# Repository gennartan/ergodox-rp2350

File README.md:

# ErgoDox Custom Keyboard

## 1. Introduction

This project is a custom split ErgoDox-style keyboard built around the RP2350
and Zephyr RTOS.

The goal is not only to build a working keyboard. It is also a learning project
for KiCad, PCB design, electronic development, Zephyr, USB HID, and split
keyboard firmware. The RP2350 is clearly more powerful than a keyboard needs,
but that is part of the fun: it gives enough room to experiment without being
limited by the controller.

The firmware is designed to keep the time between a physical key press and the
USB HID report as small as reasonably possible. Keys are scanned through direct
GPIO interrupts with debounce handling, then converted into USB HID keyboard
reports by the active half.

The keyboard is split into two hands. One half is connected to the computer over
USB and acts as the HID keyboard. The other half sends its key events over UART
to the USB-connected half.

## 2. Project Structure

The repository contains the mechanical, electronic, and firmware parts of the
keyboard.

### Mechanical files

`hardware/mechanical` contains the STL files for the printed case parts. The
current files are for the right hand; the left-hand mechanical design is made by
mirroring the right-hand design.

### Electronic files

`hardware/electronic` contains the KiCad projects for the PCBs:

- `LeftHand.kicad_pro`: left-hand PCB project;
- `RightHand.kicad_pro`: right-hand PCB project;
- `ErgoDoxCustom.kicad_pro`: shared/root KiCad project files;
- `production/v1`: generated fabrication and assembly files.

The production files were prepared for JLCPCB assembly, and the BOM contains
JLCPCB/LCSC component references. More hardware-specific notes are documented in
`hardware/electronic/README.md`.

### Zephyr firmware

The root of the repository is a Zephyr application for the RP2350:

- `CMakeLists.txt`: Zephyr application definition and target board;
- `prj.conf`: main firmware configuration;
- `Kconfig`: keyboard hand, layout, and split UART options;
- `app.overlay`: GPIO, LED, USB HID, and UART device tree configuration;
- `src/main.c`: key scanning, USB HID, split transport selection, and LED state;
- `src/keyboard_runtime.c`: layer and HID report runtime;
- `src/keyboard_layouts.c` and `src/custom_layout.c`: keyboard layouts;
- `src/split_transport_uart.c`: UART transport between the two halves;
- `layouts`: JSON layout descriptions;
- `scripts/keyboard_configurator.py`: helper UI for generating custom layouts.

## 3. How To Get Started

### Build with Docker (Linux, macOS, or Windows)

Install Docker Engine on Linux, or Docker Desktop with Linux containers on
macOS/Windows. No host Zephyr, Python, CMake, or compiler installation is needed.
Run this command from the repository root (the same command works in PowerShell):

```sh
docker compose run --build --rm build
```

Compose builds the dependency image, mounts the repository at `/workspace`, and
builds both keyboard halves. Image layers are cached. After the first build,
you can skip the image-build check with `docker compose run --rm build`.
Firmware builds run with networking disabled; image creation can access the
internet to download dependencies.

The container runs as UID/GID `1000:1000` by default. If your Linux account uses
different IDs, set `BUILD_UID` and `BUILD_GID` in a local `.env` file, using the
values printed by `id -u` and `id -g`. For a single invocation, you can use:

```sh
BUILD_UID=$(id -u) BUILD_GID=$(id -g) docker compose run --rm build
```

The Ubuntu 26.04 image contains the official Zephyr v4.5.0 stable release, its
RP2350 modules, Python build dependencies, and Zephyr SDK 1.0.1 with the ARM GNU
toolchain. The first image build needs internet access; subsequent firmware
builds use the installed dependencies and can run offline. Docker selects the native Linux architecture
on x86-64 and ARM64 hosts, including Apple Silicon.

Zephyr v4.5.0 is a stable release, not an LTS release. The current 3.7 LTS
series predates RP2350 support and cannot build this board without backports.

Both halves are built together. The final build step exports both UF2 files to
the build directory root, written back to the mounted repository. The exports
are refreshed on every successful build, even when their content is unchanged:

- `build/docker/ergodox_left.uf2`
- `build/docker/ergodox_right.uf2`

The separate `build/docker` directory avoids reusing a host build's CMake cache.
Use these commands for a clean build or an interactive development shell:

```sh
docker compose run --rm build build -p always
docker compose run --rm build bash
```

Inside that shell, the repository is `/workspace`, and the installed west
workspace is `/opt/zephyr-workspace`.

To move to another machine, clone the repository and repeat the commands above.
You can also transfer the built image without rebuilding its dependencies:

```sh
docker save -o ergodox-build.tar ergodox-build
# On another machine with the same CPU architecture:
docker load -i ergodox-build.tar
```

The Zephyr release tag and SDK version are defined by build arguments in `Dockerfile`.
Rebuild the image when changing dependencies; application source edits only need
another `docker compose run --rm build`. The Python packages and Ubuntu packages are resolved when
the image is built, so transferring the image also preserves those exact versions.
Flashing remains a host operation: copy each UF2 to the corresponding half in
BOOTSEL mode.

### Build with a host Zephyr installation

Install Zephyr and make sure `west` is available in your shell. This project is
built as a Zephyr application, so it expects the usual Zephyr SDK and Python
environment to be installed first.

From the project directory, build both keyboard halves with sysbuild:

```sh
west build --sysbuild -b rp2350b_core/rp2350b/m33
```

The board is also set in `CMakeLists.txt`, so the board argument can be omitted
once the Zephyr workspace is configured:

```sh
west build --sysbuild
```

Sysbuild compiles the application twice and selects the hand independently for
each image. The resulting UF2 files are:

```text
build/ergodox_left.uf2
build/ergodox_right.uf2
```

Flash the generated firmware using your RP flash hardware tool. The exact
command depends on the probe and runner you use, but the usual Zephyr entry
point is:

```sh
west flash --domain ergodox_left --openocd /usr/local/bin/openocd
```

Flash the right half by selecting its sysbuild domain:

```sh
west flash --domain ergodox_right --openocd /usr/local/bin/openocd
```

The USB-connected half will enumerate as the keyboard; the other half will fall
back to UART and forward its key events.

## 4. How To Create A Custom Design

Start with the layout. The firmware supports multiple hands and layers through
`src/keyboard_layout.h`. You can edit the C layout files directly, or use the
layout JSON files and `scripts/keyboard_configurator.py` to generate a custom
layout.

Useful places to change behavior:

- `layouts/custom.json`: custom layout source data;
- `src/custom_layout.c`: generated/custom C layout;
- `Kconfig`: available layout choices;
- `prj.conf`: selected hand and selected layout;
- `app.overlay`: GPIO mapping, LED pins, USB HID device, and split UART pins.

The configurator separates localized keyboard keys from special actions. Select
one of the dedicated action types for:

- consumer controls such as volume, playback, display brightness, browser,
  mail, and calculator;
- system power, sleep, and wake controls;
- mouse buttons, cursor movement, and vertical scrolling;
- keyboard lighting toggle, on/off, and brightness controls.

The generated layout uses `KB_CONSUMER`, `KB_SYSTEM`, `KB_MOUSE_*`, and
`KB_LIGHTING` macros. Keyboard, consumer, system, and mouse reports share one
HID interface and use report IDs to distinguish them. In boot protocol, only the standard eight-byte
keyboard report is sent, without a report ID. The current board drives its four
indicator LEDs as binary GPIOs, so lighting brightness up/down maps to enabled/disabled rather
than PWM dimming.

For example, exported volume keys now look like:

```c
KB_CONSUMER(HID_CONSUMER_VOLUME_INCREMENT)
KB_CONSUMER(HID_CONSUMER_VOLUME_DECREMENT)
```

For electronic changes, open the KiCad projects in `hardware/electronic`. The
left and right hands are separate projects, so changes that affect both halves
should be applied and checked on both PCBs.

For mechanical changes, start from `hardware/mechanical`. The current case files
are based on a modified right-hand design; mirror or adapt them for the left
hand as needed.

Before producing a new hardware revision:

- update the KiCad schematic and PCB;
- run electrical rules and design rules checks;
- regenerate the BOM, position files, designator files, netlist, and fabrication
  ZIP;
- store the generated files under a new production revision folder;
- update the hardware README with any known fixes or ordering notes.

## 5. How To Contribute

Contributions are welcome, especially in areas that make the keyboard easier to
build, flash, customize, or manufacture.

Good contribution topics include:

- firmware fixes and latency improvements;
- layout improvements;
- Zephyr configuration cleanup;
- KiCad schematic or PCB fixes;
- mechanical case improvements;
- clearer build, flashing, and production documentation.

When contributing, avoid committing local generated noise such as `build/`,
Python `__pycache__` folders, KiCad lock files, or editor-specific files.
Production files are useful to commit when they represent a real hardware
revision that was ordered or is ready to order.

### USB web configurator (prototype)

The `ergodox,configurator` node in `app.overlay` defines the local boot chord:

```dts
configurator {
    compatible = "ergodox,configurator";
    gpios = <&gpio0 1 (GPIO_ACTIVE_LOW | GPIO_PULL_UP)>,
            <&gpio0 2 (GPIO_ACTIVE_LOW | GPIO_PULL_UP)>;
};
```

Hold every listed input active while powering up. The default is physical keys
1 and 2 on the same half. Polarity and pulls come from each GPIO specifier.
The firmware samples the entire chord repeatedly over 20 ms before starting USB,
UART, or key interrupts. Partial chords continue normal boot. GPIO errors stop
boot rather than treating a failed read as a pressed key. Set `status = "disabled"`
or remove the node to disable this feature. Only one enabled node is supported.
Chords spanning both halves are not supported.

When the chord is held on the USB-connected half at boot, the keyboard enumerates
as **Ergodox Configurator**, a USB CDC-NCM Ethernet device. Its address is
`192.168.7.1/24`; a DHCP server offers the computer `192.168.7.2/24`, without a
default gateway or DNS server. Open **http://192.168.7.1/** to view the current layout, both physical keyboard
halves, and their layers. Select a key to inspect its action. Download the layout
as JSON or import a JSON layout file. Uploaded files are validated and
previewed before **Save to keyboard** writes NVM; reboot to apply the saved
layout. No internet connection or additional web server is needed. See the
[JSON file format](docs/layout-json.md).
The firmware loads a validated RAM layout
from NVM, with compiled factory defaults as fallback. See [configuration formats](docs/keyboard-configuration.md).

On Linux, the host uses the `cdc_ncm` driver. Allow the new Ethernet connection
to obtain an IPv4 address automatically. If the host does not run DHCP on the
new interface, assign it `192.168.7.2` with subnet mask `255.255.255.0` manually,
leaving the gateway and DNS empty. Avoid using another network with the same
subnet during configuration. Other operating systems need a compatible CDC-NCM
driver; compatibility has not yet been verified on hardware.

Configuration mode exposes only USB networking and does not send keyboard
reports. It scans the local keys and receives raw key events from the slave over
UART so the viewer can highlight physical presses on both halves at up to 20 Hz.
The slave must boot normally; hold the boot chord only on the USB-connected half. Normal keyboard boot excludes the USB
network function and does not start DHCP or HTTP. Release the chord and reconnect
USB to return to keyboard mode. RTT logs report service startup or failures.

### Logs through the SWD debug port (RTT)

Both halves send Zephyr logs on RTT channel 0. Connect the Raspberry Pi Debug
Probe's **D** port to the target's SWD debug connector (SWCLK, SWDIO, GND) and
power the keyboard normally. UART wiring is not needed.

Rebuild the Docker image once to download the manifest-pinned SEGGER module,
then flash the new firmware on the half you want to inspect:

```sh
docker compose run --build --rm build
```

For a host Zephyr installation, run `west update segger` before rebuilding.
Use a host OpenOCD installation with RP2350 and RTT support. Start it with:

```sh
openocd -f interface/cmsis-dap.cfg -f target/rp2350.cfg \
  -c "adapter speed 5000" \
  -c "init" \
  -c "targets rp2350.cm0" \
  -c "rtt setup 0x20000000 0x82000 {SEGGER RTT}" \
  -c "rtt start" \
  -c "rtt server start 19021 0"
```

In another terminal, read the logs:

```sh
nc localhost 19021
```

The search range covers the RP2350's 520 KiB SRAM. OpenOCD attaches to the
running firmware without deliberately resetting it. The 4 KiB RTT buffer holds
recent logs; messages are dropped when full so an absent debugger does not block
normal operation. Only the half connected to the probe is visible. To repeat
startup messages, reset the target and restart the OpenOCD RTT session if needed.

If OpenOCD reports that no RTT control block is found, verify that the flashed
firmware contains RTT and that the target is running. A shared-library error
before OpenOCD starts indicates a host OpenOCD installation problem.

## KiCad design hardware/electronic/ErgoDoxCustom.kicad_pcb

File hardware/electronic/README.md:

# Electronic Hardware

This folder contains the KiCad projects and production outputs for the
electronic part of the ErgoDox Custom split keyboard.

The RP2350 is clearly overkill for a keyboard controller. It was chosen
intentionally as part of the project goal: learning more about KiCad, PCB
design, and electronic development in general, rather than optimizing for the
simplest possible keyboard hardware.

The keyboard is built as two independent halves:

- `LeftHand`: PCB and schematic for the left half.
- `RightHand`: PCB and schematic for the right half.
- `ErgoDoxCustom`: shared/root KiCad project files used by the design.
- `production/v1`: generated fabrication outputs for the first hardware
  revision, split by hand.

Each hand has the same general role: scan its local switches, drive its local
indicator LEDs, and expose the split communication connector. The firmware
selects whether the build represents the left or right hand, then labels key
events before sending them to the keyboard runtime.

## Split Structure

The keyboard uses one USB-connected half and one secondary half. Since each half
has USB capabilities, each hand can act as the master (and this can optimize
cable management).

The USB-connected half enumerates as the USB HID keyboard. It handles its own
key events locally and receives key events from the other half over UART.

The secondary half scans its local keys and forwards raw key events over the
split UART link. It does not need to enumerate as a USB keyboard during normal
operation.

Both halves therefore need:

- local key switch inputs;
- local LED drive circuitry;
- power rails for the controller and peripherals;
- UART TX/RX wiring between the two halves;
- a common ground between the two halves.

## Left Hand

The left-hand hardware lives in:

- `LeftHand.kicad_pro`
- `LeftHand.kicad_sch`
- `LeftHand.kicad_pcb`
- `production/v1/LeftHand`

The left hand is one half of the split keyboard and should expose the same
functional blocks as the right hand: key inputs, LEDs, controller power, USB,
and UART split communication.

## Right Hand

The right-hand hardware lives in:

- `RightHand.kicad_pro`
- `RightHand.kicad_sch`
- `RightHand.kicad_pcb`
- `production/v1/RightHand`

The right hand is the matching half of the split keyboard. In the current
firmware layout it can also act as the USB-connected half, receiving split
events from the other side and sending the final HID report to the host.

## Known Fixes Needed

The current hardware revision still needs these corrections before the next
production release:

- Left hand: change the USB/UART power reference from `3V3` to `VBUS` (`5V`).
- Right hand: replace the NPN transistor used for the LEDs with a MOSFET.

## Production Notes

The v1 production files were prepared for JLCPCB assembly. The component
references in the BOM are therefore aligned with JLCPCB/LCSC part references,
which makes the files easier to reuse or audit when preparing another order.

As a rough reference point, producing five assembled left-hand PCBs was
estimated at about 90 EUR for this revision (5 parts ordered) excluding
the cherry-mx switch to buy separately.

Before ordering boards, regenerate and review the production files for both
hands:

- BOM CSV;
- component positions CSV;
- designators CSV;
- IPC netlist;
- fabrication ZIP.

Keep the production output grouped by hardware revision so that each ordered
PCB set can be traced back to the exact KiCad state used to generate it.

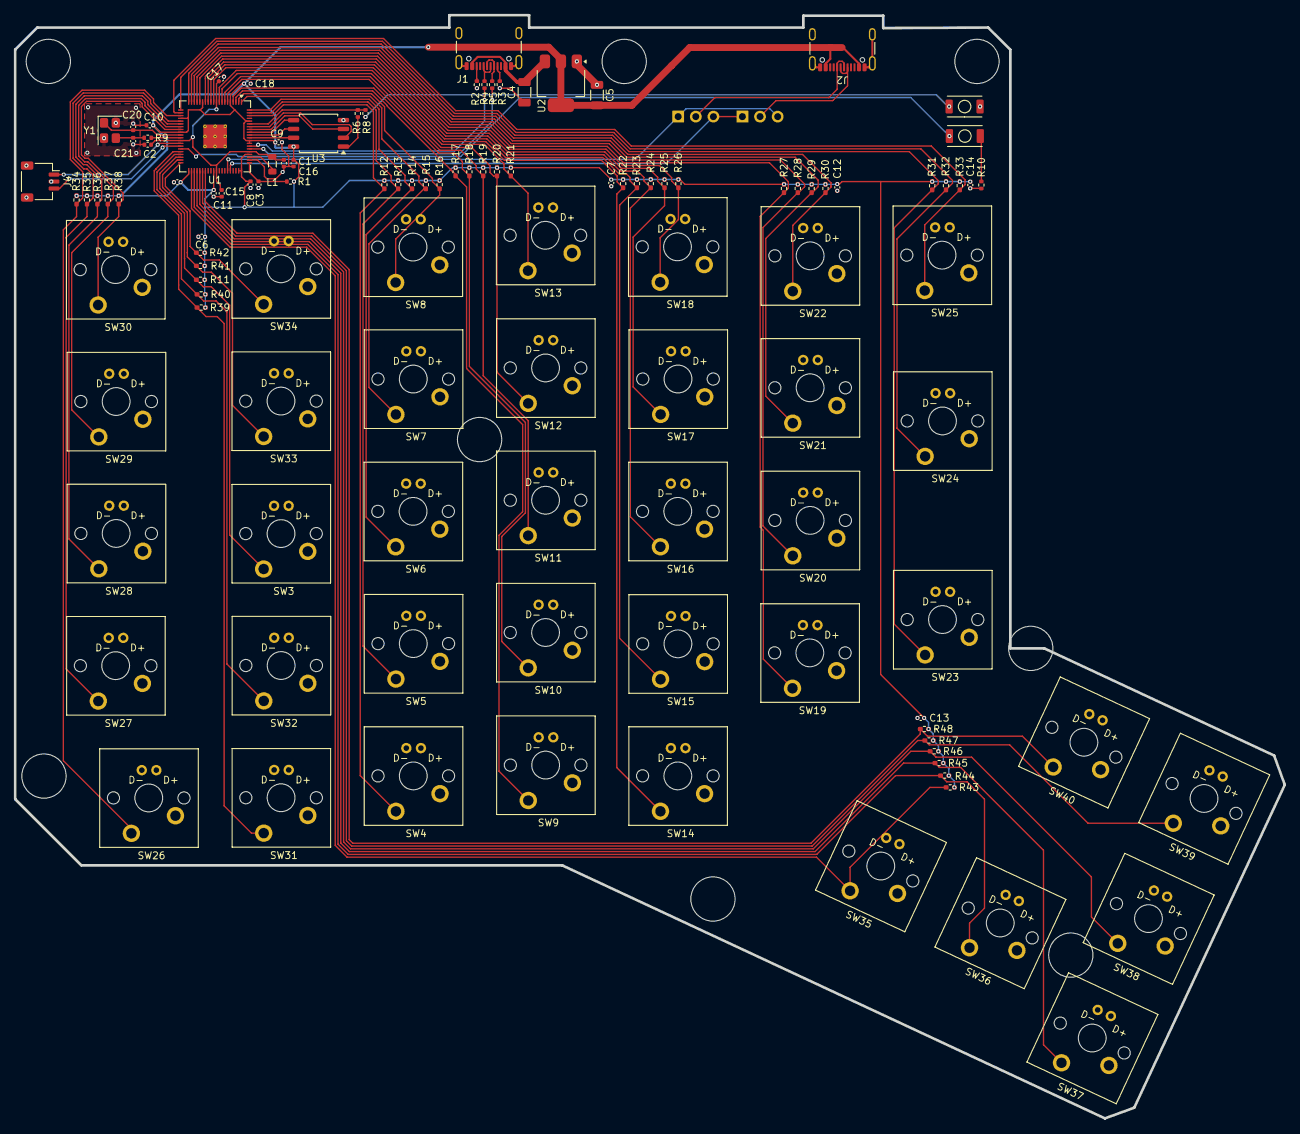
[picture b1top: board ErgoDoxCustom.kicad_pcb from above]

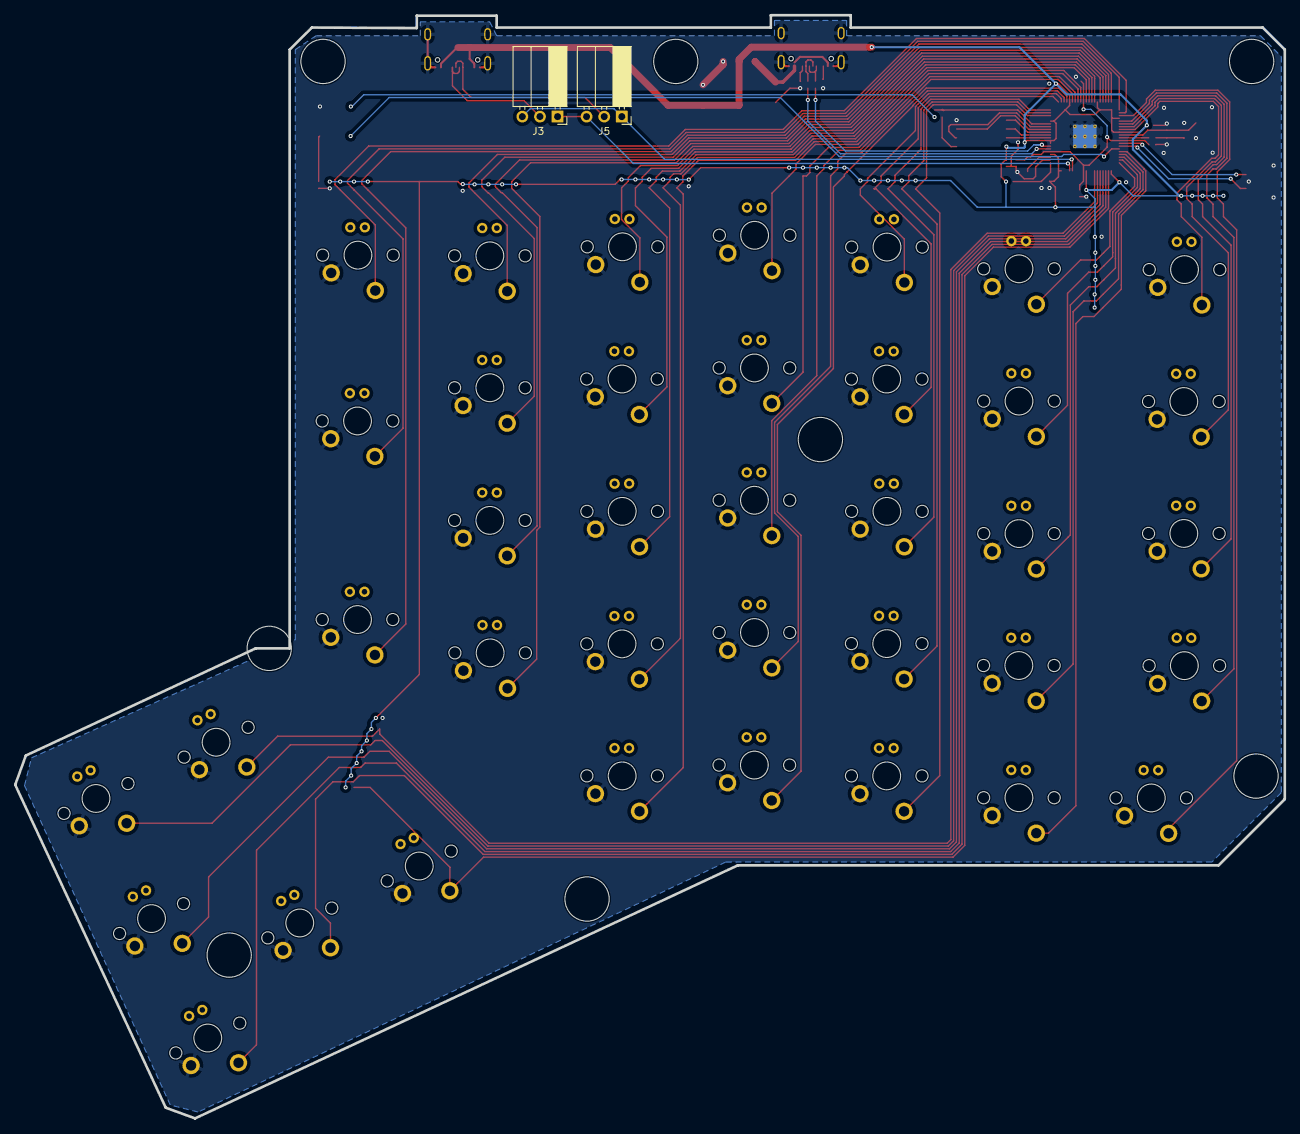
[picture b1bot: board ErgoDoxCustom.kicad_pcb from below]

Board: 2 copper layers, 182.8 x 158.9 mm, 119 parts (3 on the bottom side), 69 nets.

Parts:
C1, C2, C3, C16: 4.7u; C_0402_1005Metric
C4, C5: 10u; C_1206_3216Metric
C6, C7, C8, C9, C10, C11, C12, C13, C14, C15, C17, C18, C19: 100n; C_0402_1005Metric
C20, C21: 15p; C_0402_1005Metric
H99: MECHANICAL; ErgoDOXmech
J1, J2: USB_C_Receptacle_USB2.0_16P; USB_C_Receptacle_GCT_USB4105-xx-A_16P_TopMnt_Horizontal
J3, J5: Conn_01x03_Pin; PinSocket_1x03_P2.54mm_Horizontal
J4: Conn_01x03_MountingPin; JST_SH_SM03B-SRSS-TB_1x03-1MP_P1.00mm_Horizontal
L1: 3.3u; L_0805_2012Metric
R1, R4, R5: 33; R_0402_1005Metric
R2, R3: 5.1k; R_0402_1005Metric
R6: 0; R_0402_1005Metric
R8, R9, R10: 1k; R_0402_1005Metric
R11, R12, R13, R14, R15, R16, R17, R18, R19, R20, R21, R22, R23, R24, R25, R26, R27, R28, R29, R30, R31, R32, R33, R34, R35, R36, R37, R38, R39, R40, R41, R42, R43, R44, R45, R46, R47, R48: 10k; R_0402_1005Metric_Pad0.72x0.64mm_HandSolder
SW1, SW2: SW_Push; SW_SMD_5x3mm
SW3, SW4, SW5, SW6, SW7, SW8, SW9, SW10, SW11, SW12, SW13, SW14, SW15, SW16, SW17, SW18, SW19, SW20, SW21, SW22, SW23, SW24, SW25, SW26, SW27, SW28, SW29, SW30, SW31, SW32, SW33, SW34, SW35, SW36, SW37, SW38, SW39, SW40: SW_Push; MyCherrySwitch
U1: RP2350B-QFN80; QFN-80-1EP_10x10mm_P0.4mm_EP3.4x3.4mm_ThermalVias
U2: NCP1117-3.3_SOT223; SOT-223-3_TabPin2
U3: W25Q128JVS; SOIC-8_5.3x5.3mm_P1.27mm
Y1: Crystal_GND24; Crystal_SMD_Abracon_ABM8G-4Pin_3.2x2.5mm

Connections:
+1V1: C2.1, C15.1, C16.1, C17.1, L1.1, U1.10 (DVDD), U1.32 (DVDD), U1.51 (DVDD), U1.65 (VREG_FB)
+3.3V: C1.1, C5.2, C6.1, C7.1, C8.1, C9.1, C10.1, C11.1, C12.1, C13.1, C14.1, C18.1, C19.1, J2.A4 (VBUS), J2.A9 (VBUS), J2.B4 (VBUS), J2.B9 (VBUS), R1.1, R11.1, R12.1, R13.1, R14.1, R15.1, R16.1, R17.1, R18.1, R19.1, R20.1, R21.1, R22.1, R23.1, R24.1, R25.1, R26.1, R27.1, R28.1, R29.1, R30.1, R31.1, R32.1, R33.1, R34.1, R35.1, R36.1, R37.1, R38.1, R39.1, R40.1, R41.1, R42.1, R43.1, R44.1, R45.1, R46.1, R47.1, R48.1, U1.5 (IOVDD), U1.15 (IOVDD), U1.24 (IOVDD), U1.29 (IOVDD), U1.41 (IOVDD), U1.50 (IOVDD), U1.59 (ADC_AVDD), U1.60 (IOVDD), U1.64 (VREG_VIN), U1.68 (USB_OTP_VDD), U1.69 (QSPI_IOVDD), U1.76 (IOVDD), U2.2 (VO), U3.8 (VCC)
/Flash Memory/QSPI_CLK: U1.71 (QSPI_SCLK), U3.6 (CLK)
/Flash Memory/QSPI_SD0: U1.72 (QSPI_SD0), U3.5 (DI/IO_{0})
/Flash Memory/QSPI_SD1: U1.74 (QSPI_SD1), U3.2 (DO/IO_{1})
/Flash Memory/QSPI_SD2: U1.73 (QSPI_SD2), U3.3 (~WP/IO_{2})
/Flash Memory/QSPI_SD3: U1.70 (QSPI_SD3), U3.7 (~HOLD/~RESET/IO_{3})
/Flash Memory/QSPI_SS: R6.1, R8.2, U1.75 (QSPI_SS)
/GPIO1: R12.2, SW4.2, U1.78 (GPIO1)
/GPIO2: R13.2, SW5.2, U1.79 (GPIO2)
/GPIO3: R14.2, SW6.2, U1.80 (GPIO3)
/GPIO4: R15.2, SW7.2, U1.1 (GPIO4)
/GPIO5: R16.2, SW8.2, U1.2 (GPIO5)
/GPIO6: R17.2, SW9.2, U1.3 (GPIO6)
/GPIO7: R18.2, SW10.2, U1.4 (GPIO7)
/GPIO8: R19.2, SW11.2, U1.6 (GPIO8)
/GPIO9: R20.2, SW12.2, U1.7 (GPIO9)
/GPIO10: R21.2, SW13.2, U1.8 (GPIO10)
/GPIO11: R22.2, SW14.2, U1.9 (GPIO11)
/GPIO12: R23.2, SW15.2, U1.11 (GPIO12)
/GPIO13: R24.2, SW16.2, U1.12 (GPIO13)
/GPIO14: R25.2, SW17.2, U1.13 (GPIO14)
/GPIO15: R26.2, SW18.2, U1.14 (GPIO15)
/GPIO16: R27.2, SW19.2, U1.16 (GPIO16)
/GPIO17: R28.2, SW20.2, U1.17 (GPIO17)
/GPIO18: R29.2, SW21.2, U1.18 (GPIO18)
/GPIO19: R30.2, SW22.2, U1.19 (GPIO19)
/GPIO20: R31.2, SW23.2, U1.20 (GPIO20)
/GPIO21: R32.2, SW24.2, U1.21 (GPIO21)
/GPIO22: R33.2, SW25.2, U1.22 (GPIO22)
/GPIO23: R34.2, SW26.2, U1.23 (GPIO23)
/GPIO24: R35.2, SW27.2, U1.25 (GPIO24)
/GPIO25: R36.2, SW28.2, U1.26 (GPIO25)
/GPIO26: R37.2, SW29.2, U1.27 (GPIO26)
/GPIO27: R38.2, SW30.2, U1.28 (GPIO27)
/GPIO28: R39.2, SW31.2, U1.36 (GPIO28)
/GPIO29: R40.2, SW32.2, U1.37 (GPIO29)
/GPIO30: R11.2, SW3.2, U1.38 (GPIO30)
/GPIO31: R41.2, SW33.2, U1.39 (GPIO31)
/GPIO32: R42.2, SW34.2, U1.40 (GPIO32)
/GPIO33: R43.2, SW35.2, U1.42 (GPIO33)
/GPIO34: R44.2, SW36.2, U1.43 (GPIO34)
/GPIO35: R45.2, SW37.2, U1.44 (GPIO35)
/GPIO36: R46.2, SW38.2, U1.45 (GPIO36)
/GPIO37: R47.2, SW39.2, U1.46 (GPIO37)
/GPIO38: R48.2, SW40.2, U1.47 (GPIO38)
/Power/VREG_AVDD: C3.2, R1.2, U1.61 (VREG_AVDD)
/Power/VREG_LX: L1.2, U1.63 (VREG_LX)
/RUN: SW2.2, U1.35 (RUN)
/SWCLK: J4.1, U1.33 (SWCLK)
/SWD: J4.3, U1.34 (SWDIO)
/USB_DN: R5.1, U1.66 (USB_DM)
/USB_DP: R4.1, U1.67 (USB_DP)
GND: C1.2, C2.2, C3.1, C4.1, C5.1, C6.2, C7.2, C8.2, C9.2, C10.2, C11.2, C12.2, C13.2, C14.2, C15.2, C16.2, C17.2, C18.2, C19.2, C20.1, C21.1, J1.A1 (GND), J1.A12 (GND), J1.B1 (GND), J1.B12 (GND), J1.S1 (SHIELD), J2.A1 (GND), J2.A12 (GND), J2.B1 (GND), J2.B12 (GND), J2.S1 (SHIELD), J4.2, J4.MP (MountPin), R2.2, R3.2, R10.2, SW1.1, SW3.1, SW4.1, SW5.1, SW6.1, SW7.1, SW8.1, SW9.1, SW10.1, SW11.1, SW12.1, SW13.1, SW14.1, SW15.1, SW16.1, SW17.1, SW18.1, SW19.1, SW20.1, SW21.1, SW22.1, SW23.1, SW24.1, SW25.1, SW26.1, SW27.1, SW28.1, SW29.1, SW30.1, SW31.1, SW32.1, SW33.1, SW34.1, SW35.1, SW36.1, SW37.1, SW38.1, SW39.1, SW40.1, U1.62 (VREG_PGND), U1.81 (GND), U2.1 (GND), U3.4 (GND), Y1.2, Y1.4
unnamed: C21.2, R9.1, Y1.3
unnamed: J1.A5 (CC1), R3.1
unnamed: J1.B5 (CC2), R2.1
unnamed: J2.A7 (D-), J2.B7 (D-), J3.2
unnamed: J2.A6 (D+), J2.B6 (D+), J5.2
unnamed: R8.1, SW1.2
unnamed: R10.1, SW2.1
unnamed: C20.2, U1.30 (XIN), Y1.1
unnamed: R9.2, U1.31 (XOUT)
unnamed: R6.2, U3.1 (~CS)
UART0_RX: J3.1, J5.3, U1.56 (GPIO45_ADC5)
UART0_TX: J3.3, J5.1, U1.55 (GPIO44_ADC4)
USB_D+: J1.A6 (D+), J1.B6 (D+), R4.2
USB_D-: J1.A7 (D-), J1.B7 (D-), R5.2
VBUS: C4.2, J1.A4 (VBUS), J1.A9 (VBUS), J1.B4 (VBUS), J1.B9 (VBUS), U2.3 (VI)

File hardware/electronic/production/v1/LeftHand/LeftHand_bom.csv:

Designator,Footprint,Quantity,Value,LCSC Part #
"C1, C16, C2, C3",0402,4,4.7u,C23733
"C10, C11, C12, C13, C14, C15, C17, C18, C19, C6, C7, C8, C9",0402,13,100n,C1525
"C20, C21",0402,2,15p,C1548
"C4, C5",1206,2,10u,C13585
H99,ErgoDOXmech,1,MECHANICAL,
"J1, J2",USB_C_Receptacle_GCT_USB4105-xx-A_16P_TopMnt_Horizontal,2,USB_C_Receptacle_USB2.0_16P,C3025063
"J3, J5",PinSocket_1x03_P2.54mm_Horizontal,2,Conn_01x03_Pin,C92159
J4,JST_SH_SM03B-SRSS-TB_1x03-1MP_P1.00mm_Horizontal,1,Conn_01x03_MountingPin,C160403
L1,0805,1,3.3u,C1046
"R1, R4, R5",0402,3,33,C25105
"R10, R8, R9",0402,3,1k,C11702
"R11, R12, R13, R14, R15, R16, R17, R18, R19, R20, R21, R22, R23, R24, R25, R26, R27, R28, R29, R30, R31, R32, R33, R34, R35, R36, R37, R38, R39, R40, R41, R42, R43, R44, R45, R46, R47, R48",0402,38,10k,
"R2, R3",0402,2,5.1k,C25905
R6,0402,1,0,C17168
"SW1, SW2",SW_SMD_5x3mm,2,SW_Push,C720477
"SW10, SW11, SW12, SW13, SW14, SW15, SW16, SW17, SW18, SW19, SW20, SW21, SW22, SW23, SW24, SW25, SW26, SW27, SW28, SW29, SW3, SW30, SW31, SW32, SW33, SW34, SW35, SW36, SW37, SW38, SW39, SW4, SW40, SW5, SW6, SW7, SW8, SW9",MyCherrySwitch,38,SW_Push,
U1,QFN-80-1EP_10x10mm_P0.4mm_EP3.4x3.4mm_ThermalVias,1,RP2350B-QFN80,C42415655
U2,SOT-223-3_TabPin2,1,NCP1117-3.3_SOT223,C6186
U3,SOIC-8_5.3x5.3mm_P1.27mm,1,W25Q128JVS,C97521
Y1,Crystal_SMD_Abracon_ABM8G-4Pin_3.2x2.5mm,1,Crystal_GND24,C20625731

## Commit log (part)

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2026-04-09 Initialize keyboard from example
    Example from zephyrproject sample
2026-04-26 Add gitignore file
2026-04-26 Add basic GPIO and USB configuration
2026-05-01 Add basic LEDs control
2026-05-01 Add support for UART debug probe
2026-05-01 New USB interface support
2026-05-01 Configure GPIO interrupt instead of matrix scanning
    This allows to have a better detection of GPIO updates.
2026-05-01 Add possibility to configure keyboard layers
2026-05-01 Add basic configurator software using QT
2026-05-01 Improve GUI for keyboard configuration
2026-05-01 Remove 39th unexistant key
2026-05-01 Adapt font-size and color for GUI app
2026-05-01 Complete list of HID code based on zephyr usb hid
2026-05-01 Add selection of keyboard layout with dummy layout
2026-05-02 Configure both keyboard parts in the same file
    - Update keyboard configurator to be able to manage both keyboard part
    in the same file.
    - Update C code structure to select hand dynamically (hand not selected
    dynamically yet, this will be done later)
2026-05-02 Configure left keyboard configuration to match GPIO mapping
2026-05-02 Control LEDs with layer activation
2026-05-15 Add current custom layout
2026-05-15 refactor layout using capture option
2026-05-15 Add Capture option to keybaord configurator
2026-05-31 Disable UART for debugging
2026-05-31 Add hand selection from configuration
    Add the possibility to build for left or right hand. Doing it at build
    time ensures that once flashed, the keyboard will keep its
    configuration and that not runtime error could make it uncontrollable.
2026-05-31 Fix: change left alt keypress to left alt modifier
    Otherwise it is not used as a modifier when actually pressed.
2026-05-31 Fix GPIO position of right column for right hand
    It was inverted. Up was down, down was up...
2026-05-31 Feat: configure UART bus communication between each keyboard part
    At startup, the keyboard part will detect whether it has a USB
    connection or not. If yes, it will act as the main part and merge
    received report from UART into a USB HID report sent to the host. If
    not, it will send all key pressed into a custom UART report for the main
    part.
    This finally allows to use both keyboard parts together.
2026-06-01 fix: change font color to avoid black on black text
    Including the following texts:
    - Contextual menus (save json, ...)
    - Layers tabs (nav, base, ...)
    - Modifiers checkboxes
2026-06-01 Try to reproduce custom ergodox layout
    Based on https://configure.zsa.io/ergodox-ez/layouts/DAlAK/latest/2
2026-06-01 Feat: send key pressed instead of HID report over UART
    This allows to change the layer of one part by pressing the other part
    layer switch key.
2026-06-01 Fix right tumb layer change should switch to symbol layer
2026-06-07 Add pipfile for keyboard configurator
2026-06-07 Add STL files for printing the case
2026-06-07 Integrate kicad project into repository
    This contains 3 sub-projects
    * ErgodoxCustom: That was the initial project
    * Left hand: taken from the initial project to have a custom PCB for the
    left hand
    * Right hand: idem
2026-06-07 Rewrite README to make the project easier to onboard
2026-06-07 Add images to the README
